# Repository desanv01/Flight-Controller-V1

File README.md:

<h1 align="center">Flight Controller V1</h1>

<p align="center">Custom STM32H743 controller design and six-layer PCB implementation</p>

---

Custom STM32H743VIT6 controller developed through staged schematic capture, resource allocation, placement and a six-layer PCB routing rework. The repository preserves its engineering design, manufacturing data and development record.

**Project contributor:** [Desan Vasu](https://github.com/desanv01). Project engineering activities were performed by Desan; physical fabrication was external. Documented development: 26 August–14 September 2026. These are evidence dates, not employment dates.

> **Current status:** Engineering prototype. Fabrication data is available; assembly sourcing, stack selection and physical validation remain outstanding. No final V1 firmware build is claimed.

**Quick links:** [KiCad project](hardware/FC_REV_A.kicad_pro) · [Schematic PDF](docs/exports/schematic.pdf) · [Manufacturing](fabrication/README.md) · [Development history](docs/development/timeline.md) · [Verification](docs/validation-status.md) · [Releases](https://github.com/desanv01/Flight-Controller-V1/releases)

---

## Table of contents

- [Features](#features)
- [Hardware specifications](#hardware-specifications)
- [Architecture](#architecture)
- [Pin mapping](#pin-mapping)
- [Board layout and wiring](#board-layout-and-wiring)
- [Development history](#development-history)
- [Design and manufacturing files](#design-and-manufacturing-files)
- [Getting started](#getting-started)
- [Firmware](#firmware)
- [Verification](#verification)
- [Repository structure](#repository-structure)
- [License and credits](#license-and-credits)

---

## Features

- STM32H743VIT6 with audited core, debug and clock circuitry
- ICM-42688-P on dedicated SPI and BMP390 barometer
- External regulated power with separate main, analog, sensor and reference rails
- Four motor signal outputs; external CRSF, GNSS, telemetry and companion interfaces
- microSD logging; CAN1 and explicitly reserved/DNP optional functions
- Six copper layers with documented routing, plane-order and DNP corrections
- Native KiCad sources, local libraries, Gerbers/drills and vendor assembly data

---

## Hardware specifications

<details>
<summary>Full specifications and engineering status</summary>

| Parameter | Value |
|---|---|
| MCU | STM32H743VIT6, LQFP100 |
| PCB | 6 copper layers, 1.60 mm nominal |
| Design tool | KiCad 10.0.6 |
| Primary IMU | ICM-42688-P |
| Barometer | BMP390 |
| Power | External regulated input; exact boundary in power-and-interfaces documentation |
| USB | Data/debug; external controller power required |
| Motor signals | 4 controlled outputs |
| CAN | CAN1; optional CAN2 reserved/DNP |
| Storage | microSD |
| Board body | Approximately 104 mm square |
| Mounting | See exact source outline and holes; enlarged floorplan differs from initial 20 mm study |
| Clock | 8 MHz passive HSE crystal |
| Fabrication status | Engineering data available; final part sourcing/stack selection outstanding |

</details>

Specifications describe the design intent and source. Runtime capabilities require physical qualification; see [validation status](docs/validation-status.md).

---

## Architecture

```mermaid
flowchart LR
    POWER[External regulated supply] --> FC[STM32H743 flight controller]
    IMU[ICM42688P and BMP390] --> FC
    RC[CRSF receiver] --> FC
    GPS[External GNSS and compass] --> FC
    FC -->|Motor signals and ground| ESC[OpenESC]
    BAT[Battery and power distribution] --> ESC
    COMP[Separately powered companion] <-->|Advisory data interface| FC
    USB[USB data and debug] <--> FC
```

The controller owns stabilization, motor waveforms, arming and failsafe. Companion perception/navigation is advisory and separately powered. [Architecture and boundaries](docs/architecture.md).

---

## Pin mapping

Four motor signals use PD12–PD15 / TIM4_CH1–CH4. ICM42688P uses SPI1 and BMP390 uses I2C2. microSD is on SDMMC1. [Resource matrix](docs/pin-mapping.md).

The [connector pin tables](docs/connector-pinouts.md) are generated from the exact public netlist. Do not infer connector numbering from another version or from an unlabelled photograph.

---

## Board layout and wiring

CAD renders above represent the published source, not photographs of tested hardware. [PCB layer and assembly exports](docs/exports/README.md) · [Power and interfaces](docs/power-and-interfaces.md) · [Bring-up procedure](docs/bring-up.md).

---

## Development history

The [timeline](docs/development/timeline.md) follows requirements, resource freeze, schematic capture, correction, placement, routing and manufacturing stages. Each milestone links its evidence and tag. Publication commits use their actual import date; historical dates remain in the records.

The [development archive](archive/README.md) preserves unique CAD experiments and engineering scripts, including failed approaches. Source fragments are labelled as fragments; no missing historical source state is fabricated.

---

## Design and manufacturing files

| Material | Location |
|---|---|
| Editable current KiCad source | [hardware/](hardware/README.md) |
| Browser-readable schematic and PCB drawings | [docs/exports/](docs/exports/README.md) |
| JLCPCB engineering source and assembly data | [fabrication/jlcpcb/](fabrication/jlcpcb/README.md) |
| PCBWay engineering source and assembly data | [fabrication/pcbway/](fabrication/pcbway/README.md) |
| Downloadable source-associated bundles | [Engineering releases](https://github.com/desanv01/Flight-Controller-V1/releases) |
| Historical sources and experiments | [Archive index](archive/README.md) |

Choose one version and vendor package as a complete set. Do not mix source, Gerbers, BOM or placement files across packages. New public manifests replace original private-package hashes after neutral naming and metadata changes.

---

## Getting started

1. Download or clone this repository.
2. Install KiCad 10 with its standard symbol, footprint and 3D libraries.
3. Open [FC_REV_A.kicad_pro](hardware/FC_REV_A.kicad_pro), then the root schematic and PCB.
4. Review [hardware instructions](hardware/README.md), [verification](docs/validation-status.md) and the correct [vendor package](fabrication/README.md).
5. Review the props-off [bring-up checklist](docs/bring-up.md) before any powered hardware work.

This hardware release has no demonstrated final V1 firmware binary. Resource planning is preserved; a board-specific firmware implementation remains necessary.

---

## Firmware

See [firmware status](firmware/README.md) for resource planning and the missing final-board build.

---

## Verification

Fresh source checks: **14 October 2026**, KiCad **10.0.6**.

| Check | Result |
|---|---|
| ERC errors / warnings | 0 / 12 |
| DRC rule errors / warnings | 0 / 3 |
| Raw unconnected entries | 16 |
| Schematic parity issues | 0 |
| Physical qualification | Pending |

The 16 raw unconnected entries are intentionally isolated DNP-only endpoints; the footprint-attribute checks are included. They remain visible in raw DRC rather than being hidden as a zero-error result.

Ignored checker categories and warning dispositions are recorded in [validation status](docs/validation-status.md). EDA checks and a firmware build do not establish physical reliability or flight qualification.

---

## Repository structure

```text
hardware/       Current coherent KiCad source and libraries
firmware/       Target availability, configuration and build provenance
fabrication/    Vendor-specific source, assembly data and export instructions
docs/           Architecture, pinouts, development history and portfolio case study
media/          Exact-source CAD renders and layer views
verification/   Fresh native reports, corrections and exception evidence
tools/          Portable checking/export utilities
archive/        Recovered source states and indexed development experiments
```

---

## License and credits

Original V1 project material has no blanket redistribution license assigned in this publication; see [licensing scope](LICENSE.md). KiCad-derived libraries, ArduPilot and other third-party content retain their own notices. [Third-party notices](THIRD_PARTY_NOTICES.md).

Desan Vasu performed the project engineering activities; fabrication was external. [Contribution statement](CONTRIBUTIONS.md) · [Portfolio case study](docs/portfolio/case-study.md).

Reference projects: [ArduPilot](https://github.com/ArduPilot/ardupilot), [KiCad](https://www.kicad.org/), and the OpenESC/OpenRX ecosystem identified in the source records.

Related project: [Flight Controller V2](https://github.com/desanv01/Flight-Controller-V2).

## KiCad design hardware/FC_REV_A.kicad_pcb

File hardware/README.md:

# Hardware source

Open [FC_REV_A.kicad_pro](FC_REV_A.kicad_pro) in KiCad 10.0.6 or a compatible later version. Install KiCad's standard libraries/models. Project-local symbols, footprints and required local 3D models are bundled. Standard models use `KICAD10_3DMODEL_DIR`; local assets use `KIPRJMOD`.

PCB and project stems remain matched so DRC loads the intended rules. The source is a neutral publication copy; pad, routing, zone, placement and outline geometry was checked unchanged during descriptive metadata reconciliation. See [correction report](../verification/latest/publication-corrections.json).

The current tree matches the final V1 vendor board geometry. Read the [validation status](../docs/validation-status.md), including warning/ignored-rule and physical-test limitations.

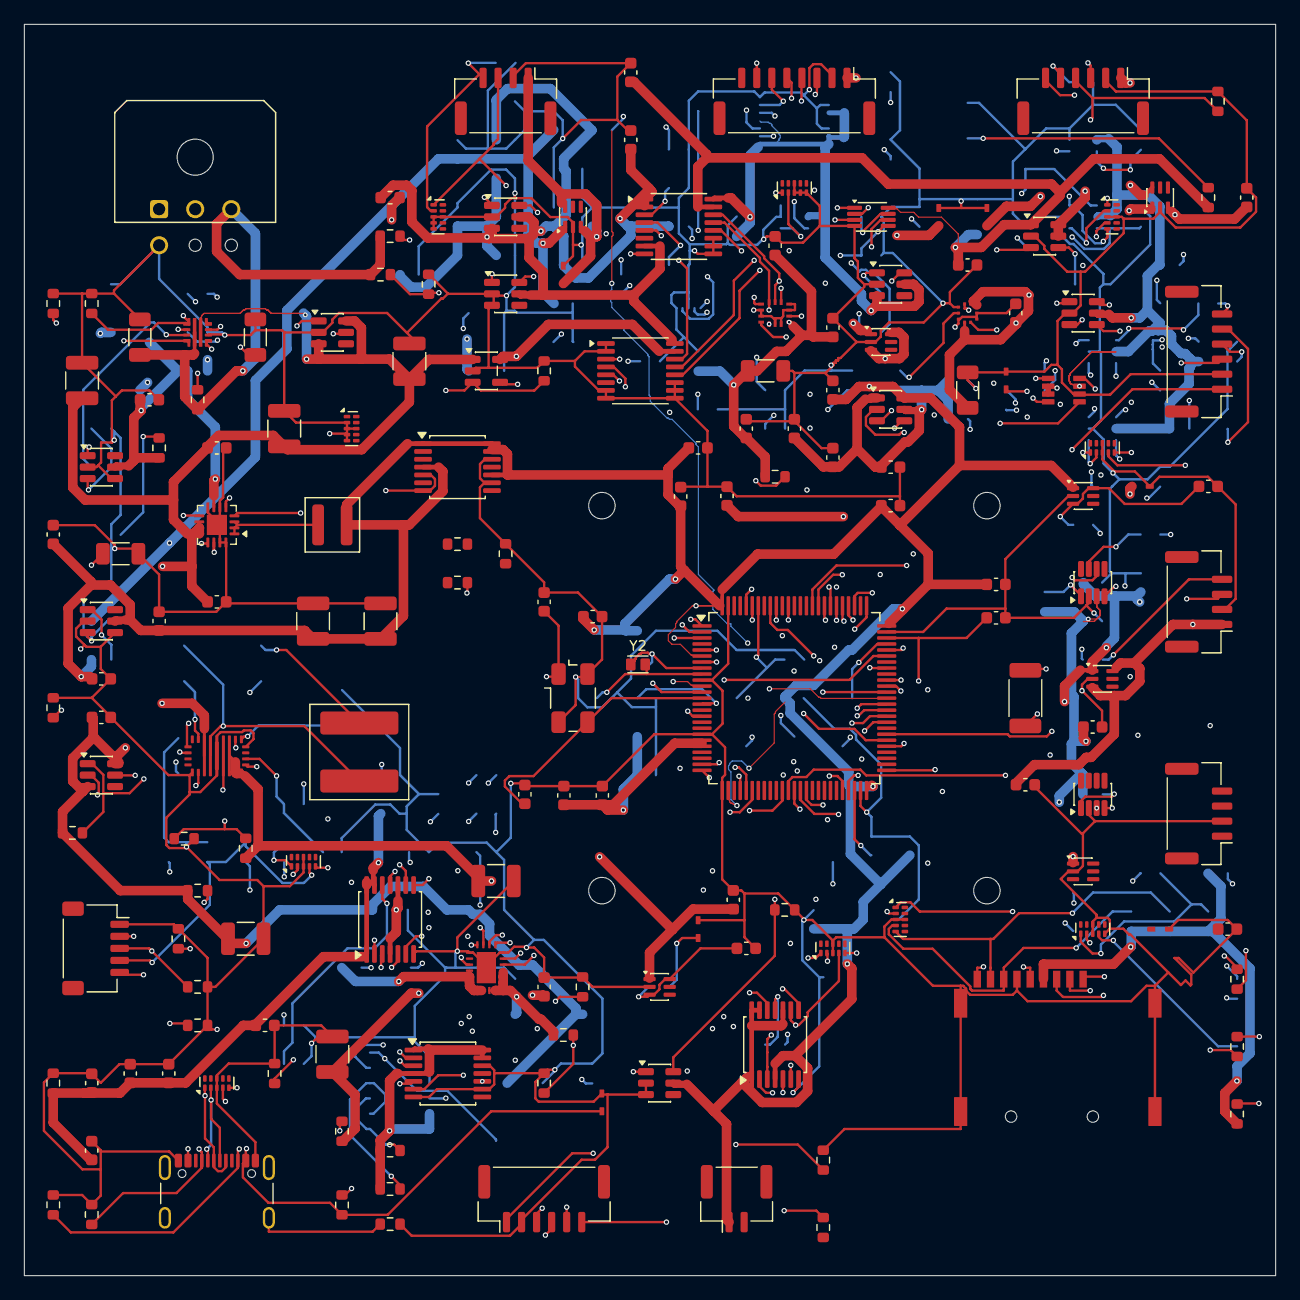
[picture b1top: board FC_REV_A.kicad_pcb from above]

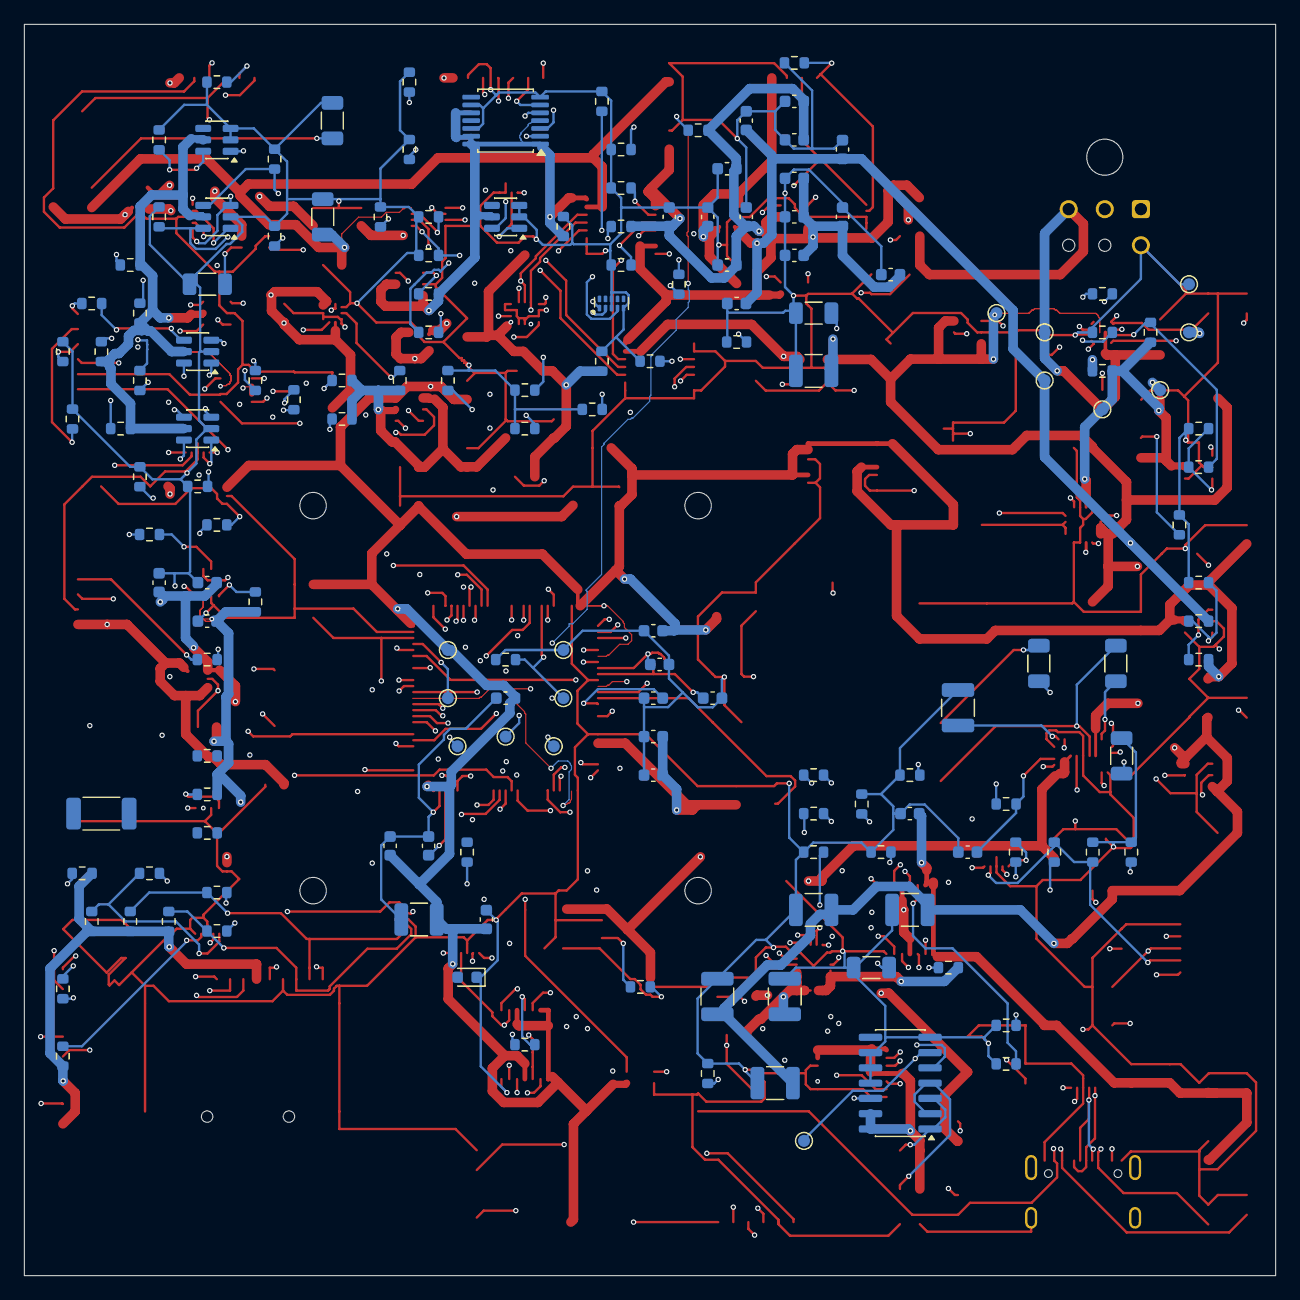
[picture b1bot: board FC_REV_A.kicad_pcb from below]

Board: 6 copper layers, 104.0 x 104.0 mm, 330 parts (159 on the bottom side), 181 nets.

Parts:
C1, C2, C3, C4, C5, C9, C11, C13, C14, C22, C26, C35, C39, C43, C44, C45, C46, C51, C54, C55, C56, C57, C62, C63, C64, C65, C66, C67, C68, C69, C70, C71, C72, C73, C74, C75, C76, C77, C78, C79, C80, C81, C82, C83, C84, C85, C86, C87, C88, C89, C90, C91, C92, C93, C94, C95, C96, C97, C98, C99, C101: 100n; Capacitor_SMD__C_0603_1608Metric
C6: 4.7u; Capacitor_SMD__C_0603_1608Metric
C7, C8: 2.2u; Capacitor_SMD__C_0603_1608Metric
C10, C12: 1u; Capacitor_SMD__C_0603_1608Metric
C15, C16: 24p; Capacitor_SMD__C_0603_1608Metric
C17, C18: TBD DNP; Capacitor_SMD__C_0603_1608Metric
C19, C20, C27, C28, C29, C38, C42: 100n; Capacitor_SMD__C_1206_3216Metric
C21, C23, C24, C25, C30, C31, C32, C33, C34, C40, C41, C47, C48, C49, C50, C100: 22u; Capacitor_SMD__C_1210_3225Metric
C36, C52: 2.2u; Capacitor_SMD__C_1206_3216Metric
C37: 4.7n; Capacitor_SMD__C_0603_1608Metric
C53: 10n; Capacitor_SMD__C_0603_1608Metric
C58, C60, C61: 1u; Capacitor_SMD__C_1206_3216Metric
C59: 22n; Capacitor_SMD__C_1206_3216Metric
D1: GREEN optional; LED_SMD__LED_0603_1608Metric
FB1: 600R@100MHz; Inductor_SMD__L_0603_1608Metric
H1, H2, H3, H4: M2_2.2mm_PROVISIONAL
J3: RC_IN; Connector_JST__JST_GH_BM04B-GHS-TBT_1x04-1MP_P1.25mm_Vertic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
J4: GPS1; Connector_JST__JST_GH_BM08B-GHS-TBT_1x08-1MP_P1.25mm_Vertic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
J5: TELEM1; Connector_JST__JST_GH_BM06B-GHS-TBT_1x06-1MP_P1.25mm_Vertic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
J6: COMPANION; Connector_JST__JST_GH_BM06B-GHS-TBT_1x06-1MP_P1.25mm_Vertic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
J7: CAN1; Connector_JST__JST_GH_BM04B-GHS-TBT_1x04-1MP_P1.25mm_Vertic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
J8: CAN2_EVAL; Connector_JST__JST_GH_BM04B-GHS-TBT_1x04-1MP_P1.25mm_Vertic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
J9: USB-C GCT USB4105; GCT_USB4105_GF_A_095_S1_S4
J10: SWD probe / target powered; Connector_JST__JST_GH_BM06B-GHS-TBT_1x06-1MP_P1.25mm_Vertic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
J11: BOOT service shunt DNP; Connector_JST__JST_GH_BM02B-GHS-TBT_1x02-1MP_P1.25mm_Vertic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
J12: microSD GCT MEM2075; GCT_MEM2075_00_140_01_A
J_ESC_FC: SM05B-SRSS-TB; ESC_JST_SH_SM05B_SRSS_TB
J_POWER1: 43045-0600; POWER1_Molex_43045_0600_4Electrical_2NPTH
L1: 2.2u; Inductor_SMD__L_Coilcraft_XAL4020-XXX
L2: 6.8u; Inductor_SMD__L_Coilcraft_XAL7070-XXX
R1, R3, R5, R9, R12, R13, R15, R20, R22, R25, R32, R34, R37, R100, R104: 10k; Resistor_SMD__R_0603_1608Metric
R2: 28.7k; Resistor_SMD__R_0603_1608Metric
R4: 37.4k; Resistor_SMD__R_0603_1608Metric
R6: 732; Resistor_SMD__R_0603_1608Metric
R7: 100; Resistor_SMD__R_0603_1608Metric
R8, R10, R28, R31, R33, R36, R38, R42, R43, R44, R45, R46, R48, R69: 100k; Resistor_SMD__R_0603_1608Metric
R11: 31.2k; Resistor_SMD__R_0603_1608Metric
R14: 31.6k; Resistor_SMD__R_0603_1608Metric
R16, R30: 49.9k; Resistor_SMD__R_0603_1608Metric
R17, R47, R117: 680; Resistor_SMD__R_0603_1608Metric
R18: 71.5k; Resistor_SMD__R_0603_1608Metric
R19, R24: 34.8k; Resistor_SMD__R_0603_1608Metric
R21: 45.3k; Resistor_SMD__R_0603_1608Metric
R23, R71, R108, R116, R130: 1k; Resistor_SMD__R_0603_1608Metric
R26, R35: 220k; Resistor_SMD__R_0603_1608Metric
R27, R58, R61, R64, R67, R101, R102, R105, R106, R113, R114, R119, R121, R123, R125, R127: 0; Resistor_SMD__R_0603_1608Metric
R29: 137k; Resistor_SMD__R_0603_1608Metric
R39, R40, R53: 1.5M; Resistor_SMD__R_0603_1608Metric
R41: 300; Resistor_SMD__R_0603_1608Metric
R49: 910; Resistor_SMD__R_0603_1608Metric
R50, R51: 4.7k; Resistor_SMD__R_0603_1608Metric
R52, R54, R55, R56, R70, R75, R79, R83, R87, R91, R95, R98, R110: 22k; Resistor_SMD__R_0603_1608Metric
R57, R59, R60, R62, R63, R65, R66, R68, R72, R74, R76, R78, R80, R82, R84, R86, R88, R90, R92, R94, R96, R97, R109, R120, R122, R124, R126, R128, R129: 47k; Resistor_SMD__R_0603_1608Metric
R73, R77, R81, R85, R89, R93: 47; Resistor_SMD__R_0603_1608Metric
R99, R115: 3.3k; Resistor_SMD__R_0603_1608Metric
R103, R107: 120; Resistor_SMD__R_2010_5025Metric
R111, R112: 5.1k; Resistor_SMD__R_0603_1608Metric
R118: 22; Resistor_SMD__R_0603_1608Metric
TP1: NRST; TestPoint__TestPoint_Pad_D1.0mm
TP2: BOOT0; TestPoint__TestPoint_Pad_D1.0mm
TP3: SWDIO; TestPoint__TestPoint_Pad_D1.0mm
TP4: SWCLK; TestPoint__TestPoint_Pad_D1.0mm
TP5: SWO; TestPoint__TestPoint_Pad_D1.0mm
TP6, TP15: GND; TestPoint__TestPoint_Pad_D1.0mm
TP7: 3V3_REF; TestPoint__TestPoint_Pad_D1.0mm
TP8: 5V_FC_IN; TestPoint__TestPoint_Pad_D1.0mm
TP9: 5V_FC_PROTECTED; TestPoint__TestPoint_Pad_D1.0mm
TP10: 5V_AUX; TestPoint__TestPoint_Pad_D1.0mm
TP11: 3V3_MAIN; TestPoint__TestPoint_Pad_D1.0mm
TP12: 3V3_SENS; TestPoint__TestPoint_Pad_D1.0mm
TP13: 3V3_ANA; TestPoint__TestPoint_Pad_D1.0mm
TP14: PWR_STATUS; TestPoint__TestPoint_Pad_D1.0mm
U1: STM32H743VIT6; Package_QFP__LQFP-100_14x14mm_P0.5mm
U2: TPS259470LRPWR; TI_RPW0010_HotRod_2x2
U3, U11: TPS3808G01DBVR; Package_TO_SOT_SMD__SOT-23-6
U4: TPS62130ARGTR; Package_DFN_QFN__VQFN-16-1EP_3x3mm_P0.5mm_EP1.68x1.68mm
U5: TPS552892RYQR; TI_RYQ0021_HotRod_5x3
U6: TPS25940LRVCR; Package_DFN_QFN__Texas_RVC0020A_WQFN-20-1EP_3x4mm_P0.5mm_EP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
U7: TPS73633DBVR; Package_TO_SOT_SMD__SOT-23-5
U8: SN74HCS11DR; Package_SO__SOIC-14_3.9x8.7mm_P1.27mm
U9, U10: TPS3700DDCR; Package_TO_SOT_SMD__SOT-23-6
U12: ICM-42688-P; TDK_ICM42688P_LGA14_3x2.5
U13, U19: SN74AXC4T774PWR; Package_SO__TSSOP-16_4.4x5mm_P0.65mm
U14: SN74AUP3G17DCUR; Package_SO__VSSOP-8_2.3x2mm_P0.5mm
U15: TPS22918DBVR; Package_TO_SOT_SMD__SOT-23-6
U16: BMP390; Bosch_BMP390_LGA10_2x2
U17: TCA9416DDFR; TI_DDF0008_SOT23THIN_8
U18: SN74AXC1T45DBVR; Package_TO_SOT_SMD__SOT-23-6
U20, U22, U42, U54, U57: TMUX1511PWR; Package_SO__TSSOP-14_4.4x5mm_P0.65mm
U21, U23, U26, U29, U32, U35, U43, U53, U58, U61, U62: TPD4E05U06DQAR; Package_SON__USON-10_2.5x1.0mm_P0.5mm
U24, U27, U30, U33: SN74LVC2G07DBVR; Package_TO_SOT_SMD__SOT-23-6
U25, U28, U31, U34, U44, U55: SN74LVC2G34DBVR; Package_TO_SOT_SMD__SOT-23-6
U36, U37, U38, U45, U48, U51, U59: LM66100DCKR; Package_TO_SOT_SMD__SOT-363_SC-70-6
U39, U40, U41, U46, U49, U52, U56, U60: TPD1E05U06DYAR; TI_DYA0002_SOD523
U47, U50: TCAN332DCNR; Package_TO_SOT_SMD__SOT-23-8
Y1: 8.000MHz; Crystal__Crystal_SMD_Abracon_ABM3B-4Pin_5.0x3.2mm
Y2: 32.768kHz DNP; Crystal_SMD_1610-2Pin_1.6x1.0mm

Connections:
3V3_REF: C1.1, C2.1, C3.1, C4.1, C5.1, C6.1, C13.1, C23.1, C24.1, C43.1, C44.1, C45.1, C46.1, C54.1, C57.1, C65.1, C67.1, C69.1, C70.1, C71.1, C72.1, C73.1, C74.1, C75.1, C76.1, C77.1, C78.1, C85.1, C86.1, C87.1, C89.1, C92.1, C95.1, C96.1, C97.1, C98.1, C100.1, C101.1, FB1.1, J11.1, J12.4, L1.2, R11.1, R13.1, R27.1, R28.1, R33.1, R34.1, R42.1, R47.1, R72.1, R76.1, R80.1, R84.1, R88.1, R92.1, R100.1, R104.1, R117.1, R120.1, R122.1, R124.1, R126.1, R128.1, R129.1, TP7.1, TP11.1, U1.6, U1.11, U1.27, U1.50, U1.75, U1.100, U4.7, U4.14, U8.13, U8.14, U9.5, U10.5, U13.1, U13.2, U13.7, U13.16, U17.7, U18.6, U19.16, U20.1, U20.4, U20.10, U20.13, U20.14, U22.1, U22.4, U22.10, U22.13, U22.14, U24.3, U24.5, U25.5, U27.3, U27.5, U28.5, U30.5, U31.5, U33.5, U34.5, U42.1, U42.4, U42.10, U42.13, U42.14, U44.5, U45.1, U47.3, U50.3, U54.1, U54.4, U54.10, U54.13, U54.14, U55.5, U57.1, U57.4, U57.10, U57.13, U57.14, U59.1
5V_FC_IN_A: C19.1, J_POWER1.1, J_POWER1.3, R2.1, R4.1, R8.1, TP8.1, U2.5
/3V3_SENS: C41.1, C51.1, C52.1, C53.1, C55.1, C56.1, C58.1, C68.1, R38.1, R41.1, R48.1, TP12.1, U7.5, U12.5, U12.8, U13.15, U14.8, U15.1, U19.15
/5V_AUX: C39.1, C79.1, C81.1, C83.1, C90.1, C93.1, R24.1, R31.1, TP10.1, U6.4, U6.5, U6.6, U6.7, U6.8, U36.1, U37.1, U38.1, U48.1, U51.1
/BOOT0: R1.1, R116.2, TP2.1, U1.94
/CAN1_RX: U1.81, U47.4
/CAN1_TX: R100.2, U1.82, U47.1
/CAN2_EVAL_RX: U1.91, U50.4
/CAN2_EVAL_TX: R104.2, U1.92, U50.1
/CAN interfaces/CAN1_5V_OUT: C91.1, J7.1, U48.3, U48.6, U49.1
/CAN interfaces/CAN1_CANH: J7.3, R101.2, R103.1
/CAN interfaces/CAN1_CANL: J7.4, R102.2, R103.2
/CAN interfaces/CAN1_H_INT: R101.1, U47.7
/CAN interfaces/CAN1_L_INT: R102.1, U47.6
/CAN interfaces/CAN2_EVAL_5V_OUT: C94.1, J8.1, U51.3, U51.6, U52.1
/CAN interfaces/CAN2_EVAL_CANH: J8.3, R105.2, R107.1
/CAN interfaces/CAN2_EVAL_CANL: J8.4, R106.2, R107.2
/CAN interfaces/CAN2_EVAL_H_INT: R105.1, U50.7
/CAN interfaces/CAN2_EVAL_L_INT: R106.1, U50.6
/COMPANION_CTS: R95.1, U1.40, U34.4
/COMPANION_RTS: R92.2, U1.39, U33.3
/COMPANION_RX: R91.1, U1.37, U34.6
/COMPANION_TX: R88.2, U1.38, U33.1
/ESC signal boundary/ESC_CURR_FILTER: R69.2, R70.1, U22.2
/ESC signal boundary/ESC_CURR_ISO: R71.1, U22.3
/ESC signal boundary/ESC_CURR_RAW: R69.1, U23.1
/ESC signal boundary/ESC_M1_ISO: R58.1, U20.3
/ESC signal boundary/ESC_M1_PORT: J_ESC_FC.2, R58.2, R59.1, U21.1
/ESC signal boundary/ESC_M2_ISO: R61.1, U20.6
/ESC signal boundary/ESC_M2_PORT: J_ESC_FC.3, R61.2, R62.1, U21.2
/ESC signal boundary/ESC_M3_ISO: R64.1, U20.8
/ESC signal boundary/ESC_M3_PORT: J_ESC_FC.4, R64.2, R65.1, U21.4
/ESC signal boundary/ESC_M4_ISO: R67.1, U20.11
/ESC signal boundary/ESC_M4_PORT: J_ESC_FC.5, R67.2, R68.1, U21.5
/ESC_CURR_DNP: R71.2, U1.16
/ESC_M1: R57.1, U1.59, U20.2
/ESC_M2: R60.1, U1.60, U20.5
/ESC_M3: R63.1, U1.61, U20.9
/ESC_M4: R66.1, U1.62, U20.12
/External UART and I2C ports/COMPANION_CTS_PORT: J6.5, R94.1, U34.3, U35.5
/External UART and I2C ports/COMPANION_RTS_OD: R93.1, U33.4
/External UART and I2C ports/COMPANION_RTS_PORT: J6.6, R93.2, U35.4
/External UART and I2C ports/COMPANION_RX_PORT: J6.4, R90.1, U34.1, U35.2
/External UART and I2C ports/COMPANION_TX_OD: R89.1, U33.6
/External UART and I2C ports/COMPANION_TX_PORT: J6.3, R89.2, U35.1
/External UART and I2C ports/COMP_REF_BLOCK: C88.1, R99.1, U45.3, U45.6
/External UART and I2C ports/COMP_REF_OUT: J6.1, R99.2, U46.1
/External UART and I2C ports/GPS1_PPS_PORT: J4.7, U43.4, U44.1
/External UART and I2C ports/GPS1_RX_PORT: J4.4, R78.1, U28.1, U29.2
/External UART and I2C ports/GPS1_SCL_PORT: J4.5, U42.3, U43.1
/External UART and I2C ports/GPS1_SDA_PORT: J4.6, U42.6, U43.2
/External UART and I2C ports/GPS1_TX_OD: R77.1, U27.6
/External UART and I2C ports/GPS1_TX_PORT: J4.3, R77.2, U29.1
/External UART and I2C ports/GPS_5V_OUT: C82.1, J4.1, U37.3, U37.6, U40.1
/External UART and I2C ports/RC_5V_OUT: C80.1, J3.1, U36.3, U36.6, U39.1
/External UART and I2C ports/RC_IN_RX_PORT: J3.4, R74.1, U25.1, U26.2
/External UART and I2C ports/RC_IN_TX_OD: R73.1, U24.6
/External UART and I2C ports/RC_IN_TX_PORT: J3.3, R73.2, U26.1
/External UART and I2C ports/TELEM1_CTS_PORT: J5.5, R86.1, U31.3, U32.5
/External UART and I2C ports/TELEM1_RTS_OD: R85.1, U30.4
/External UART and I2C ports/TELEM1_RTS_PORT: J5.6, R85.2, U32.4
/External UART and I2C ports/TELEM1_RX_PORT: J5.4, R82.1, U31.1, U32.2
/External UART and I2C ports/TELEM1_TX_OD: R81.1, U30.6
/External UART and I2C ports/TELEM1_TX_PORT: J5.3, R81.2, U32.1
/External UART and I2C ports/TELEM_5V_OUT: C84.1, J5.1, U38.3, U38.6, U41.1
/GND: C1.2, C2.2, C3.2, C4.2, C5.2, C6.2, C7.2, C8.2, C9.2, C10.2, C11.2, C12.2, C13.2, C14.2, C15.2, C16.2, C17.2, C18.2, C19.2, C20.2, C21.2, C22.2, C23.2, C24.2, C25.2, C26.2, C27.2, C30.2, C31.2, C32.2, C33.2, C34.2, C35.2, C36.2, C37.2, C38.2, C39.2, C40.2, C41.2, C42.2, C43.2, C44.2, C45.2, C46.2, C47.2, C48.2, C49.2, C50.2, C51.2, C52.2, C53.2, C54.2, C55.2, C56.2, C57.2, C58.2, C59.2, C60.2, C61.2, C62.2, C63.2, C64.2, C65.2, C66.2, C67.2, C68.2, C69.2, C70.2, C71.2, C72.2, C73.2, C74.2, C75.2, C76.2, C77.2, C78.2, C79.2, C80.2, C81.2, C82.2, C83.2, C84.2, C85.2, C86.2, C87.2, C88.2, C89.2, C90.2, C91.2, C92.2, C93.2, C94.2, C95.2, C96.2, C97.2, C98.2, C99.2, C100.2, C101.2, D1.1, J3.2, J4.2, J5.2, J6.2, J7.2, J8.2, J9.A1, J9.A12, J9.B1, J9.B12, J10.2, J12.6, J12.SH, J_ESC_FC.1, J_POWER1.2, J_POWER1.4, R1.2, R3.2, R5.2, R6.2, R9.2, R12.2, R15.2, R16.2, R18.2, R20.2, R22.2, R23.2, R25.2, R26.2, R30.2, R32.2, R35.2, R37.2, R39.2, R40.2, R41.2, R43.2, R44.2, R45.2, R46.2, R47.2, R49.2, R52.2, R53.2, R54.2, R55.2, R56.2, R57.2, R59.2, R60.2, R62.2, R63.2, R65.2, R66.2, R68.2, R70.2, R74.2, R75.2, R78.2, R79.2, R82.2, R83.2, R86.2, R87.2, R90.2, R91.2, R94.2, R95.2, R96.2, R97.2, R98.2, R109.2, R110.2, R111.2, R112.2, R113.2, R117.2, TP6.1, TP15.1, U1.10, U1.19, U1.26, U1.49, U1.74, U1.99, U2.8, U3.2, U4.6, U4.8, U4.15, U4.16, U4.17, U5.5, U5.9, U5.17, U6.1, U6.16, U6.21, U7.2, U8.7, U8.9, U8.10, U8.11, U9.2, U9.4, U10.2, U10.4, U11.2, U12.2, U12.3, U12.6, U12.7, U12.10, U12.11, U13.8, U13.9, U13.10, U13.11, U14.4, U15.2, U16.3, U16.5, U16.8, U16.9, U17.6, U18.2, U19.1, U19.2, U19.7, U19.8, U19.9, U19.10, U19.11, U20.7, U21.3, U21.8, U22.5, U22.7, U22.9, U22.12, U23.2, U23.3, U23.4, U23.5, U23.8, U24.2, U25.2, U25.3, U26.3, U26.4, U26.5, U26.8, U27.2, U28.2, U28.3, U29.3, U29.4, U29.5, U29.8, U30.2, U31.2, U32.3, U32.8, U33.2, U34.2, U35.3, U35.8, U36.2, U37.2, U38.2, U39.2, U40.2, U41.2, U42.7, U42.9, U42.12, U43.3, U43.5, U43.8, U44.2, U44.3, U45.2, U46.2, U47.2, U48.2, U49.2, U50.2, U51.2, U52.2, U53.3, U53.8, U54.7, U54.9, U54.12, U55.2, U55.3, U56.2, U57.7, U58.3, U58.8, U59.2, U60.2, U61.3, U61.8, U62.3, U62.5, U62.8, Y1.2, Y1.4
/GPS1_PPS: R98.1, U1.57, U44.6
/GPS1_RX: R79.1, U1.56, U28.6
/GPS1_SCL: R96.1, U1.95, U42.2
/GPS1_SDA: R97.1, U1.96, U42.5
/GPS1_TX: R76.2, U1.55, U27.1
/Local sensors/BARO_3V3: C61.1, C62.1, C63.1, C64.1, C66.1, R49.1, R50.1, R51.1, U15.5, U15.6, U16.1, U16.6, U16.10, U17.2, U17.3, U18.1, U18.5
/Local sensors/BARO_CT: C59.1, U15.4
/Local sensors/BARO_INT_LOCAL: R52.1, U16.7, U18.3
/Local sensors/BARO_ON: C60.1, R48.2, U15.3
/Local sensors/BARO_SCL: R50.2, U16.2, U17.1
/Local sensors/BARO_SDA: R51.2, U16.4, U17.4
/Local sensors/IMU1_CS: R42.2, U1.2, U13.5
/Local sensors/IMU_CS_N: R38.2, U12.12, U13.12
/Local sensors/IMU_INT1_BUF: R55.1, U14.5, U19.13
/Local sensors/IMU_INT1_LOCAL: R39.1, U12.4, U14.3
/Local sensors/IMU_INT2_BUF: R56.1, U14.2, U19.12
/Local sensors/IMU_INT2_LOCAL: R40.1, U12.9, U14.6
/Local sensors/IMU_MISO: R53.1, U12.1, U14.1
/Local sensors/IMU_MISO_BUF: R54.1, U14.7, U19.14
/Local sensors/IMU_MOSI: R46.1, U12.14, U13.13
/Local sensors/IMU_SCK: R45.1, U12.13, U13.14
/Local sensors/SPI1_MOSI: R44.1, U1.31, U13.4
/Local sensors/SPI1_SCK: R43.1, U1.29, U13.3
/NRST: C14.1, TP1.1, U1.14, U57.8
/Power and monitoring/3V3_ANA: C9.1, C10.1, C11.1, C12.1, FB1.2, R27.2, TP13.1, U1.20, U1.21
/Power and monitoring/5V_AUX_REG: C30.1, C31.1, C32.1, R14.1, R19.1, R21.1, U5.11, U5.12, U5.13, U6.9, U6.10, U6.11, U6.12, U6.13
/Power and monitoring/5V_FC_PROTECTED: C21.1, C22.1, C25.1, C26.1, C33.1, C35.1, C40.1, C47.1, C48.1, C49.1, C50.1, R10.1, R36.1, TP9.1, U2.6, U3.3, U3.6, U4.10, U4.11, U4.12, U5.7, U7.1, U11.3, U11.6
/Power and monitoring/AUX_BOOT1: C28.1, U5.20
/Power and monitoring/AUX_BOOT2: C29.1, U5.19
/Power and monitoring/AUX_COMP: C37.1, R17.1, U5.15
/Power and monitoring/AUX_COMP_C: C36.1, R17.2
/Power and monitoring/AUX_DVDT: C38.1, U6.18
/Power and monitoring/AUX_FB: R14.2, R15.1, U5.14
/Power and monitoring/AUX_FSW: R16.1, U5.6
/Power and monitoring/AUX_HEALTH: R34.2, U6.20, U8.5, U10.1
/Power and monitoring/AUX_HEALTH_SENSE: R31.2, R32.1, U10.3
/Power and monitoring/AUX_ILIM: R18.1, U6.17
/Power and monitoring/AUX_IMON: R23.1, U6.19
/Power and monitoring/AUX_OV: R21.2, R22.1, U6.15
/Power and monitoring/AUX_PGTH: R24.2, R25.1, U6.3
/Power and monitoring/AUX_SW1: C28.2, L2.1, U5.8
/Power and monitoring/AUX_SW2: C29.2, L2.2, U5.10
/Power and monitoring/AUX_UV: R19.2, R20.1, U6.14
/Power and monitoring/AUX_VCC: C34.1, U5.2, U5.18
/Power and monitoring/INPUT_HEALTH: R33.2, U2.4, U8.2, U8.4, U9.1
/Power and monitoring/INPUT_HEALTH_SENSE: R29.2, R30.1, U9.3
/Power and monitoring/IN_AUXOFF: R28.2, R29.1, U2.3
/Power and monitoring/IN_DVDT: R7.1, U2.7
/Power and monitoring/IN_DVDT_C: C20.1, R7.2
/Power and monitoring/IN_ILM: R6.1, U2.9
/Power and monitoring/IN_OV: R4.2, R5.1, U2.2
/Power and monitoring/IN_UV: R2.2, R3.1, U2.1
/Power and monitoring/MAIN_FB: R11.2, R12.1, U4.5
/Power and monitoring/MAIN_PG: R13.2, U4.4, U8.1, U8.3
/Power and monitoring/MAIN_SS: C27.1, U4.9
/Power and monitoring/MAIN_SW: L1.1, U4.1, U4.2, U4.3
/Power and monitoring/POWER_RUN: R10.2, U3.1, U4.13, U5.1, U11.1
/Power and monitoring/PROT_SENSE: R36.2, R37.1, U11.5
/Power and monitoring/PWR_STATUS: R35.1, TP14.1, U1.36, U8.6
/Power and monitoring/SENS_EN: R26.1, U7.3, U8.12
/Power and monitoring/SENS_NR: C42.1, U7.4
/Power and monitoring/START_SENSE: R8.2, R9.1, U3.5
/RC_IN_RX: R75.1, U1.64, U25.6
/RC_IN_TX: R72.2, U1.63, U24.1
/SDMMC1_CLK: R118.1, U1.80
/SDMMC1_CMD: R119.1, U1.83
/SDMMC1_D0: R121.1, U1.65
/SDMMC1_D1: R123.1, U1.66
/SDMMC1_D2: R125.1, U1.78
/SDMMC1_D3: R127.1, U1.79
/SD_CARD_DETECT: J12.CD, R129.2, U1.51, U62.4
/STATUS_LED: R130.1, U1.5
/STM32H743 core/BARO_INT: U1.7, U18.4
/STM32H743 core/HSE_IN: C15.1, U1.12, Y1.1
/STM32H743 core/HSE_OUT: C16.1, U1.13, Y1.3
/STM32H743 core/I2C2_SCL: U1.46, U17.8
/STM32H743 core/I2C2_SDA: U1.47, U17.5
/STM32H743 core/IMU1_DRDY: U1.3, U19.4
/STM32H743 core/IMU1_INT2: U1.1, U19.5
/STM32H743 core/LSE_IN: C17.1, U1.8, Y2.1
/STM32H743 core/LSE_OUT: C18.1, U1.9, Y2.2
/STM32H743 core/SPI1_MISO: U1.30, U19.3
/STM32H743 core/VCAP: C7.1, C8.1, U1.48, U1.73
/SWCLK: TP4.1, U1.76, U57.6
/SWDIO: TP3.1, U1.72, U57.3
/SWO: R114.2, TP5.1, U1.89
/Storage and status/LED_A: D1.2, R130.2
/Storage and status/SD_CLK_PORT: J12.5, R118.2, U61.1
/Storage and status/SD_CMD_PORT: J12.3, R119.2, R120.2, U61.2
/Storage and status/SD_D0_PORT: J12.7, R121.2, R122.2, U61.4
/Storage and status/SD_D1_PORT: J12.8, R123.2, R124.2, U61.5
/Storage and status/SD_D2_PORT: J12.1, R125.2, R126.2, U62.1
/Storage and status/SD_D3_PORT: J12.2, R127.2, R128.2, U62.2
/TELEM1_CTS: R87.1, U1.84, U31.4
/TELEM1_RTS: R84.2, U1.85, U30.3
/TELEM1_RX: R83.1, U1.25, U31.6
/TELEM1_TX: R80.2, U1.24, U30.1
/USB and debug/BOOT_SERVICE: J11.2, R116.1
/USB and debug/NRST_PORT: J10.5, U57.9, U58.4
/USB and debug/SWCLK_PORT: J10.4, U57.5, U58.2
/USB and debug/SWDIO_PORT: J10.3, U57.2, U58.1
/USB and debug/SWD_REF_BLOCK: C99.1, R115.1, U59.3, U59.6
/USB and debug/SWD_REF_OUT: J10.1, R115.2, U60.1
/USB and debug/SWO_OPT: R114.1, U57.11
/USB and debug/SWO_PORT: J10.6, U57.12, U58.5
/USB and debug/USB_CC1: J9.A5, R111.1, U53.4
/USB and debug/USB_CC2: J9.B5, R112.1, U53.5
/USB and debug/USB_DM_PORT: J9.A7, J9.B7, U53.2, U54.5
/USB and debug/USB_DP_PORT: J9.A6, J9.B6, U53.1, U54.2
/USB and debug/USB_SHIELD: J9.S1, J9.S2, J9.S3, J9.S4, R113.1
/USB and debug/USB_VBUS_LIMIT: R108.2, R109.1, U55.1
/USB and debug/USB_VBUS_PORT: J9.A4, J9.A9, J9.B4, J9.B9, R108.1, U56.1
/USB_DM: U1.70, U54.6
/USB_DP: U1.71, U54.3
/USB_VBUS: R110.1, U1.68, U55.6
